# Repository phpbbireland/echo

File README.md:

# echo (Keyboards)
This is the final repository for all prior keyboard development code, and hardware.

Models included are: 
+ Alya: ayla80 (iso/ansi)
+ Cashel: cashel100 (ansi/iso)
+ Mioke: xpad (macro/num pad)
+ Echo: test code for RP2040 ayla80 (iso).
+ EN015_60_AKL (iso)
+ EN014 (iso) June 2025

The current STM32F411 keyboard code works for all versions, however, the RGB is not tested, to put it simply, I don't know how to implement the RGB code as including it resulted in compile errors, best use the RP2040 modulesfor now.  

Moved on to version 2.x of the Keyboard Development Modules (these have a single 34 pin 1.27mm pitch (small) connector), otherwise they are the same...

**Latest Updates**  
I have switched to my RP2040 Development Module as everything works perfectly, no more issues with RGB...  
Going forward, I will use this for all development but may revisit my STM32F411 development board later...

**Important Notes**  
On all my Keyboad PCB's, the 34 pin connetor is mounted on component side (bottom) of PCB.  
On moules with a 34 pin connector, it is mounted on ***bottom*** of PCB, not the component side (top), see image below.  

**Revision C**  

**Revision D**

*Updates:*  
+ Connector now mounted on component side...  
+ Orinitation change 90°...

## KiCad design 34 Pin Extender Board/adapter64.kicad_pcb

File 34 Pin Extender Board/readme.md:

# Extender Board  

34 pin 1.27mm connector to 2 x 20 pin 2.54mm header adapter board.  
Kicad files included...
Gerber files update, previous has mirrored silkscreen...

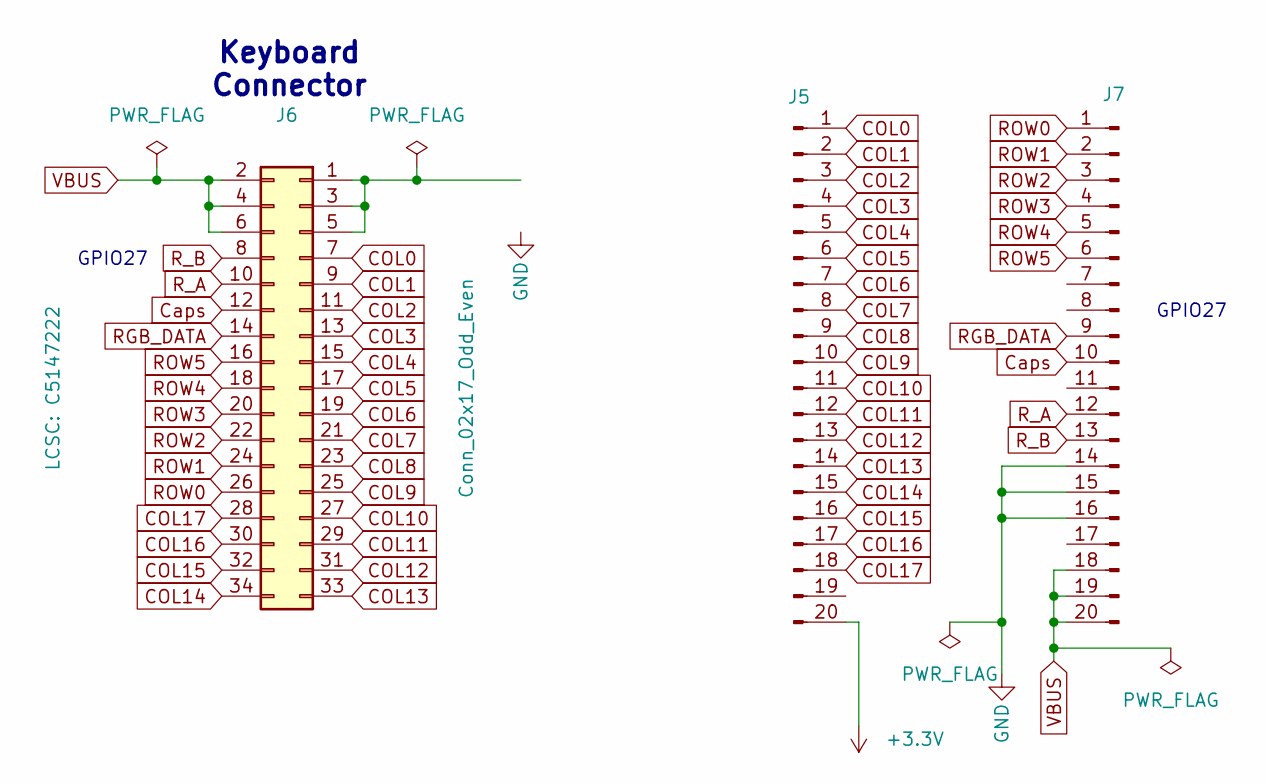
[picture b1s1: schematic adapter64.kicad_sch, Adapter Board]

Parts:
J5, J7: Conn_01x21_Pin; PinSocket_1x21_P2.54mm_Vertical
J6: Conn_02x17_Odd_Even; IDC_2X17_1.27MM; LCSC C5147222

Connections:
+3.3V: J5.20
COL0: J5.1, J6.7
COL1: J5.2, J6.9
COL2: J5.3, J6.11
COL3: J5.4, J6.13
COL4: J5.5, J6.15
COL5: J5.6, J6.17
COL6: J5.7, J6.19
COL7: J5.8, J6.21
COL8: J5.9, J6.23
COL9: J5.10, J6.25
COL10: J5.11, J6.27
COL11: J5.12, J6.29
COL12: J5.13, J6.31
COL13: J5.14, J6.33
COL14: J5.15, J6.34
COL15: J5.16, J6.32
COL16: J5.17, J6.30
COL17: J5.18, J6.28
Caps: J6.12, J7.10
GND: J7.14, J7.15, J7.16
unnamed: J6.1, J6.3, J6.5
RGB_DATA: J6.14, J7.9
ROW0: J6.26, J7.1
ROW1: J6.24, J7.2
ROW2: J6.22, J7.3
ROW3: J6.20, J7.4
ROW4: J6.18, J7.5
ROW5: J6.16, J7.6
R_A: J6.10, J7.12
R_B: J6.8, J7.13
VBUS: J6.2, J6.4, J6.6, J7.18, J7.19, J7.20

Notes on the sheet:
Keyboard Connector
GPIO27

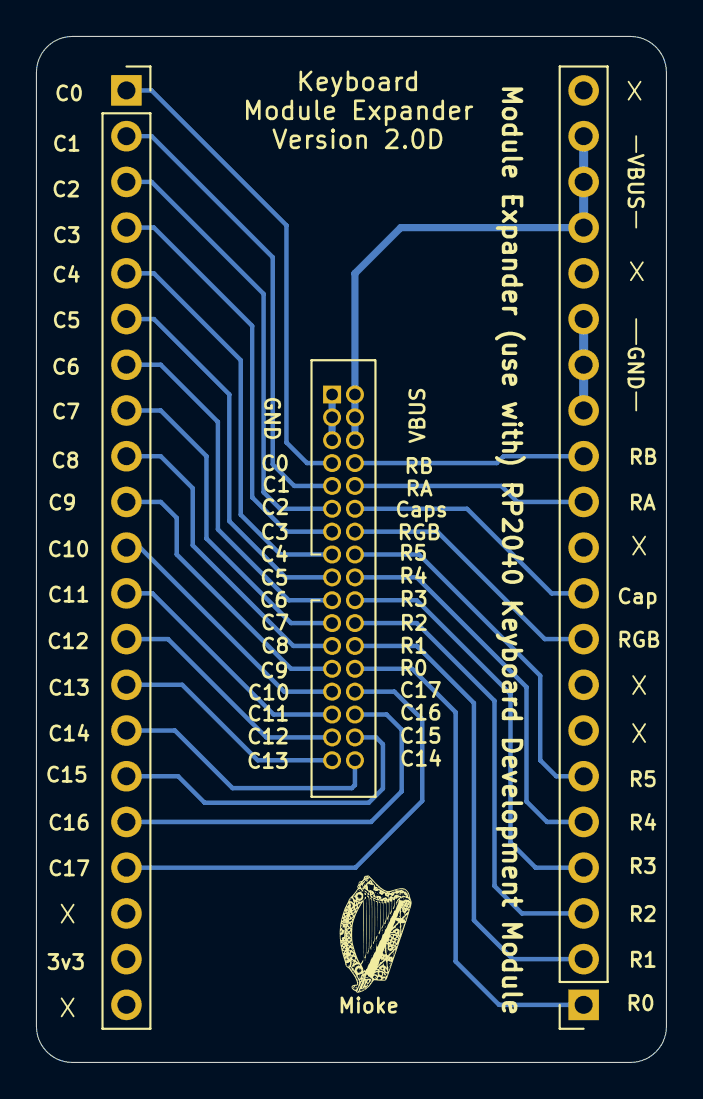
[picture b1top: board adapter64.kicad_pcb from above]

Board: 2 copper layers, 35.0 x 57.0 mm, 3 parts (0 on the bottom side), 31 nets.

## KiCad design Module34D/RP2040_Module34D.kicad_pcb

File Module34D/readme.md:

**Version D**

Micros: RP2040  

Software Supported QMK/VIA: [Link](https://github.com/phpbbireland/echo/tree/main/E014/qmk)  
Switches: MX type hot-swappable  
Keys: Up to 119 Keys (including Macro Keys) + Encoder Switch  
Rotary Encoder: Volume / RGB.  

Tested with [Basic Keyboard](https://github.com/phpbbireland/echo/tree/main/E014)

There are three Keyboard Modules (latest Rev 2D) to give away, thanks to PCBWay, if you are interested in trying out the module, contact me at my [Hackaday Link](https://hackaday.io/project/198392-keyboard-development-module-qmk-via)  

**These files may have updates, please check pin naming and orintation before prooceeding***  
I will update as time allows...

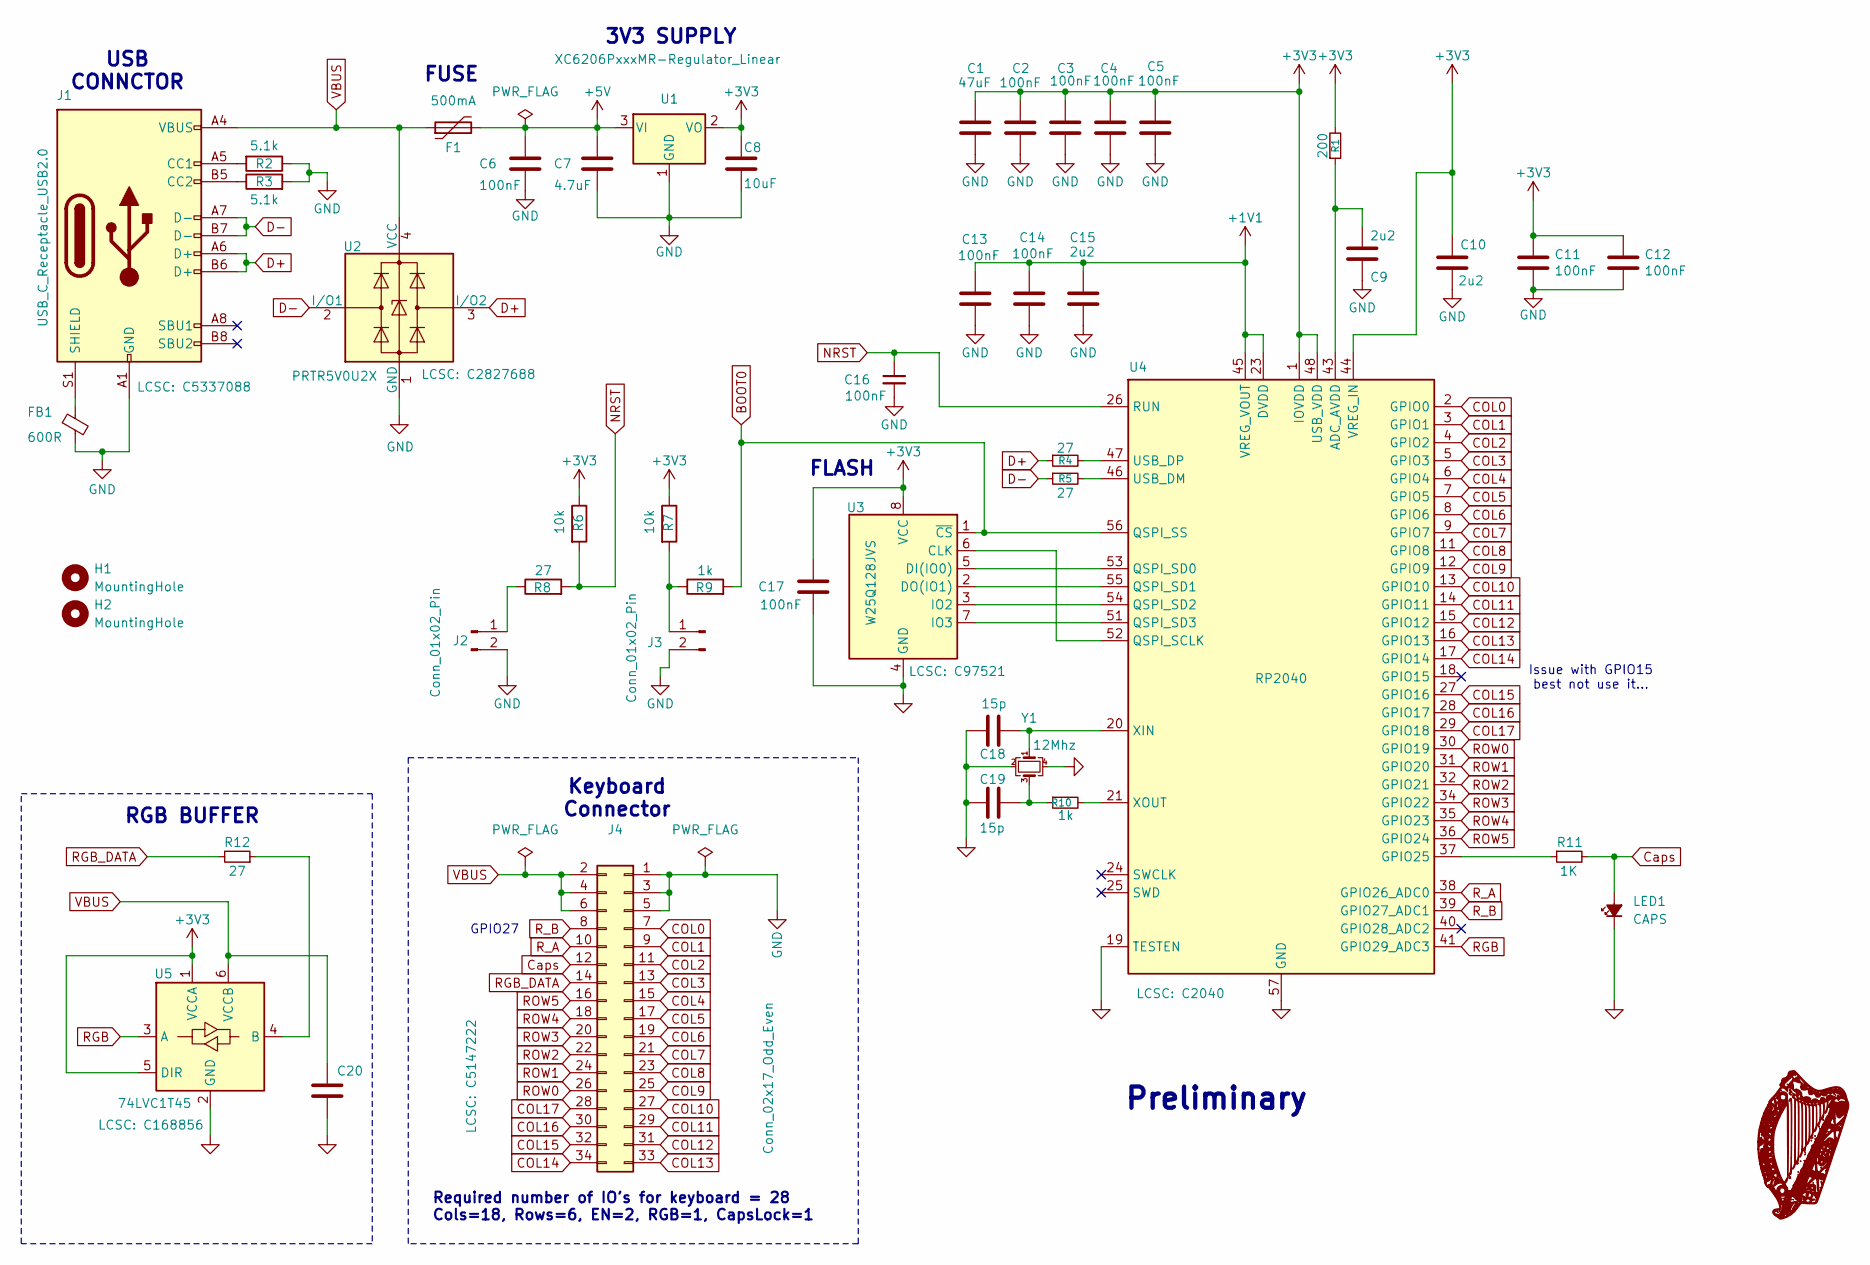
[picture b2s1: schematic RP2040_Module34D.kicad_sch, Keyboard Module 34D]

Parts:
C1: 47uF; C_0805_2012Metric; MPN# CL21A476MQYNNNE; LCSC C16780
C2, C3, C4, C11, C12, C13, C14, C20: 100nF; C_0402_1005Metric; MPN# CL05B104KB54PNC; LCSC C307331
C5, C16, C17: 100nF; C_0402_1005Metric; LCSC C307331
C6: 100nF; C_0402_1005Metric; MPN CL05B104KB54PNC; LCSC C307331
C7: 4.7uF; C_0805_2012Metric; MPN# CL21A475KAQNNNE; LCSC C1779
C8: 10uF; C_0805_2012Metric; LCSC C307331
C9, C10, C15: 2u2; C_0805_2012Metric; MPN# CL21B225KAFNNNE; LCSC C19110
C18: 15p; C_0402_1005Metric; MPN# CL05C150JB5NNNC; LCSC C86285
C19: 15p; C_0402_1005Metric; MPN# CL05C150JB5NNNC; LCSC C307331 OR C86285
F1: 500mA; Fuse_1206_3216Metric; MPN# ASMD1206-150; LCSC C135341
FB1: 600R; BEADC1608X95N; MPN# BLM18AG601SN1D; LCSC C19330
H1, H2: MountingHole; MountingHole_2.2mm_M2
J1: USB_C_Receptacle_USB2.0; USB_C_31-M-12; JlcRotOffset 180
J2, J3: Conn_01x02_Pin; PinHeader_1x02_P2.54mm_Vertical
J4: Conn_02x17_Odd_Even; IDC_2X17_1.27MM; MPN# X1270WV-2x17B-6TV01; LCSC C5147222
LED1: CAPS; LED_0805_2012Metric; MPN# D-B080508B1-KS2; LCSC C108412
R1: 200; R_0402_1005Metric; LCSC# C25087
R2: 5.1k; R_0402_1005Metric; MPN# 0402WGF5101TCE
R3: 5.1k; R_0402_1005Metric; MPN# 0402WGF5101TCE; LCSC C25905
R4, R5: 27; R_0402_1005Metric
R6: 10k; R_0402_1005Metric; MPN# 0402WGF1002TCE; LCSC C25744
R7: 10k; R_0402_1005Metric
R8: 27; R_0402_1005Metric; MPN# 0402WGF270JTCE
R9, R10: 1k; R_0402_1005Metric; MPN# 0402WGF1001TCE; LCSC C11702
R11: 1K; R_0402_1005Metric; MPN# 0402WGF1001TCE; LCSC C11702
R12: 27; R_0402_1005Metric; LCSC C25100
U1: XC6206PxxxMR-Regulator_Linear; SOT-23; LCSC C5446
U2: PRTR5V0U2X; SOT-143; LCSC C2827688
U3: W25Q128JVS; SOIC_128JVSIQ_WIN; Mfr. Part # W25Q128JVSIQ; LCSC C97521
U4: RP2040; QFN-56-1EP_7x7mm_P0.4mm_EP3.2x3.2mm; LCSC C2040
U5: 74LVC1T45; SOT-26; MPN # 74LVC1T45W6-7; JLCPCB_CORRECTION 0; 0; 270
Y1: 12Mhz; Crystal_SMD_3225-4Pin_3.2x2.5mm; LCSC C20625731

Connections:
+1V1: C13.1, C14.1, C15.1, U4.23 (DVDD), U4.45 (VREG_VOUT), U4.50 (DVDD)
+3V3: C1.1, C2.1, C3.1, C4.1, C5.1, C8.1, C10.1, C11.1, C12.1, C17.1, R1.2, R6.1, R7.1, U1.2 (VO), U3.8 (VCC), U4.1 (IOVDD), U4.10 (IOVDD), U4.22 (IOVDD), U4.33 (IOVDD), U4.42 (IOVDD), U4.44 (VREG_IN), U4.48 (USB_VDD), U4.49 (IOVDD), U5.1 (VCCA), U5.5 (DIR)
+5V: C6.1, C7.1, F1.2, U1.3 (VI)
BOOT0: R9.2, U3.1 (~CS), U4.56 (QSPI_SS)
COL0: J4.7, U4.2 (GPIO0)
COL1: J4.9, U4.3 (GPIO1)
COL2: J4.11, U4.4 (GPIO2)
COL3: J4.13, U4.5 (GPIO3)
COL4: J4.15, U4.6 (GPIO4)
COL5: J4.17, U4.7 (GPIO5)
COL6: J4.19, U4.8 (GPIO6)
COL7: J4.21, U4.9 (GPIO7)
COL8: J4.23, U4.11 (GPIO8)
COL9: J4.25, U4.12 (GPIO9)
COL10: J4.27, U4.13 (GPIO10)
COL11: J4.29, U4.14 (GPIO11)
COL12: J4.31, U4.15 (GPIO12)
COL13: J4.33, U4.16 (GPIO13)
COL14: J4.34, U4.17 (GPIO14)
COL15: J4.32, U4.27 (GPIO16)
COL16: J4.30, U4.28 (GPIO17)
COL17: J4.28, U4.29 (GPIO18)
Caps: J4.12, LED1.2 (A), R11.2
D+: J1.A6 (D+), J1.B6 (D+), R4.1, U2.3 (I/O2)
D-: J1.A7 (D-), J1.B7 (D-), R5.1, U2.2 (I/O1)
GND: C1.2, C2.2, C3.2, C4.2, C5.2, C6.2, C7.2, C8.2, C9.2, C10.2, C11.2, C12.2, C13.2, C14.2, C15.2, C16.2, C17.2, C18.2, C19.2, C20.2, FB1.2, J1.A1 (GND), J1.A12 (GND), J1.B1 (GND), J1.B12 (GND), J2.2, J3.2, J4.1, J4.3, J4.5, LED1.1 (K), R2.1, R3.2, U1.1 (GND), U2.1 (GND), U3.4 (GND), U4.19 (TESTEN), U4.57 (GND), U5.2 (GND), Y1.2, Y1.4
NRST: C16.1, R6.2, R8.2, U4.26 (RUN)
unnamed: C19.1, R10.1, Y1.3
unnamed: J1.A5 (CC1), R2.2
unnamed: J1.B5 (CC2), R3.1
unnamed: FB1.1, J1.S1 (SHIELD)
unnamed: J2.1, R8.1
unnamed: J3.1, R7.2, R9.1
unnamed: U3.6 (CLK), U4.52 (QSPI_SCLK)
unnamed: U3.5 (DI(IO0)), U4.53 (QSPI_SD0)
unnamed: U3.2 (DO(IO1)), U4.55 (QSPI_SD1)
unnamed: U3.3 (IO2), U4.54 (QSPI_SD2)
unnamed: U3.7 (IO3), U4.51 (QSPI_SD3)
unnamed: C9.1, R1.1, U4.43 (ADC_AVDD)
unnamed: R11.1, U4.37 (GPIO25)
unnamed: R5.2, U4.46 (USB_DM)
unnamed: R4.2, U4.47 (USB_DP)
unnamed: C18.1, U4.20 (XIN), Y1.1
unnamed: R10.2, U4.21 (XOUT)
unnamed: R12.1, U5.4 (B)
RGB: U4.41 (GPIO29_ADC3), U5.3 (A)
RGB_DATA: J4.14, R12.2
ROW0: J4.26, U4.30 (GPIO19)
ROW1: J4.24, U4.31 (GPIO20)
ROW2: J4.22, U4.32 (GPIO21)
ROW3: J4.20, U4.34 (GPIO22)
ROW4: J4.18, U4.35 (GPIO23)
ROW5: J4.16, U4.36 (GPIO24)
R_A: J4.10, U4.38 (GPIO26_ADC0)
R_B: J4.8, U4.39 (GPIO27_ADC1)
VBUS: C20.1, F1.1, J1.A4 (VBUS), J1.A9 (VBUS), J1.B4 (VBUS), J1.B9 (VBUS), J4.2, J4.4, J4.6, U2.4 (VCC), U5.6 (VCCB)

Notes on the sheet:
Preliminary
FLASH
FUSE
Keyboard Connector
Issue with GPIO15 best not use it...
3V3 SUPPLY
USB CONNCTOR
GPIO27
RGB BUFFER
Required number of IO's for keyboard = 28 Cols=18, Rows=6, EN=2, RGB=1, CapsLock=1

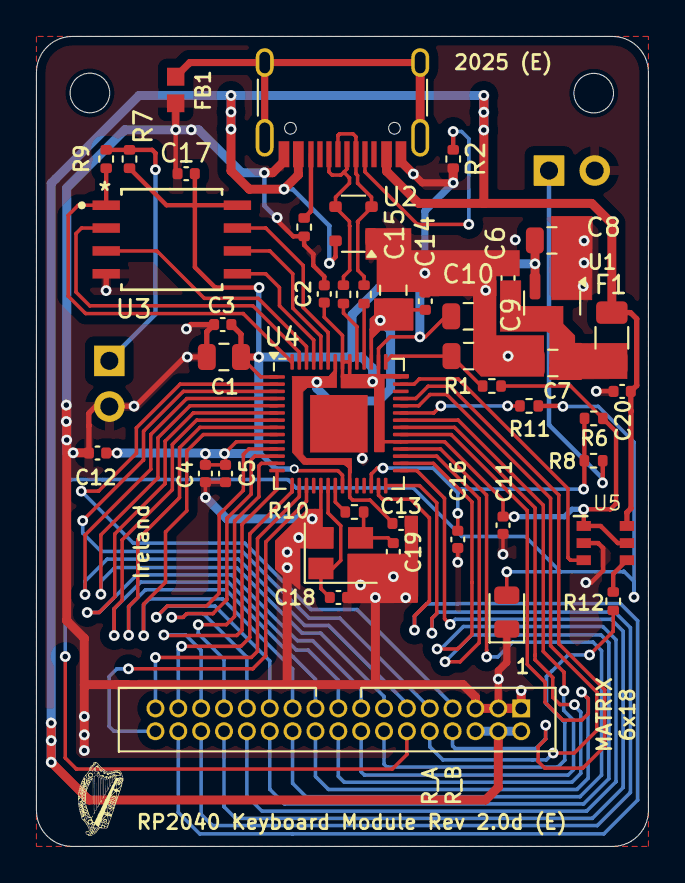
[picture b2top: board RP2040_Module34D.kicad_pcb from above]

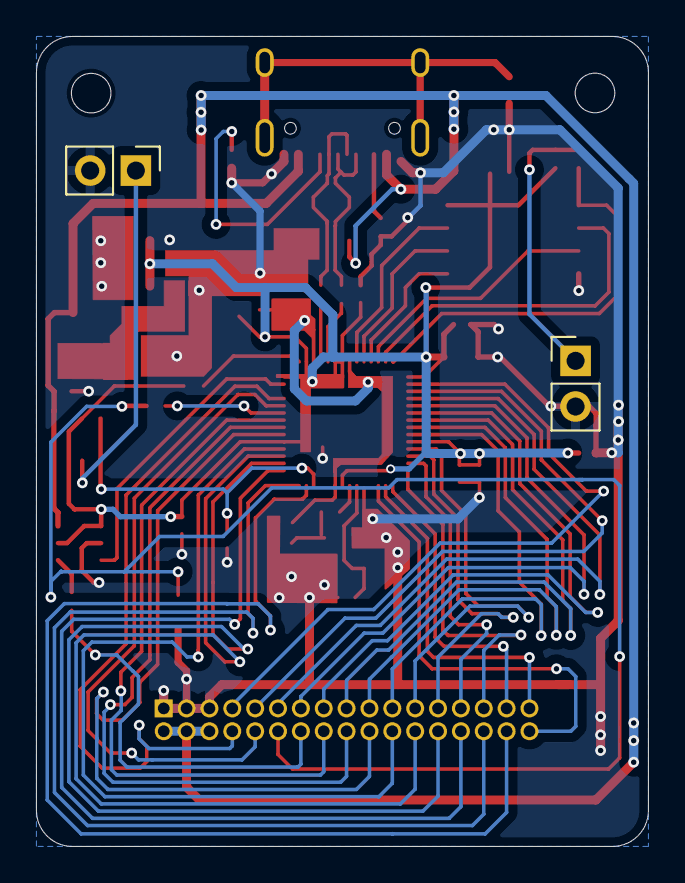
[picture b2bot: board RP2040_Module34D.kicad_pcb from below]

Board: 2 copper layers, 34.0 x 45.0 mm, 47 parts (2 on the bottom side), 56 nets.

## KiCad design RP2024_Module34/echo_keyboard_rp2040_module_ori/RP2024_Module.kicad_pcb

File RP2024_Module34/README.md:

# echo
Files to build the Basic Keyboard and RP2040 Keyboard Development Module

These have been tested with the current code and work flawlessly...
Included: 
+ RP2040_Fullsize_PCBWay_barebones... Basic Keyboard files used in all testing...
+ echo_keyboard_rp2040_module... Slightly smaller module, not produced yet...
+ echo_keyboard_rp2040_module_ori... This is the fully tested module I used in the build. [Image](https://github.com/phpbbireland/echo/blob/main/RP2024_Module34/images/RP2024_Module_Rev0.1.png)
+ iso_encoder_rp2040_en017_brd2...   The QMK and Via code for the project...

A couple of these boards are available (version 1.0, the one with the four RGB leds on it) just contact me...

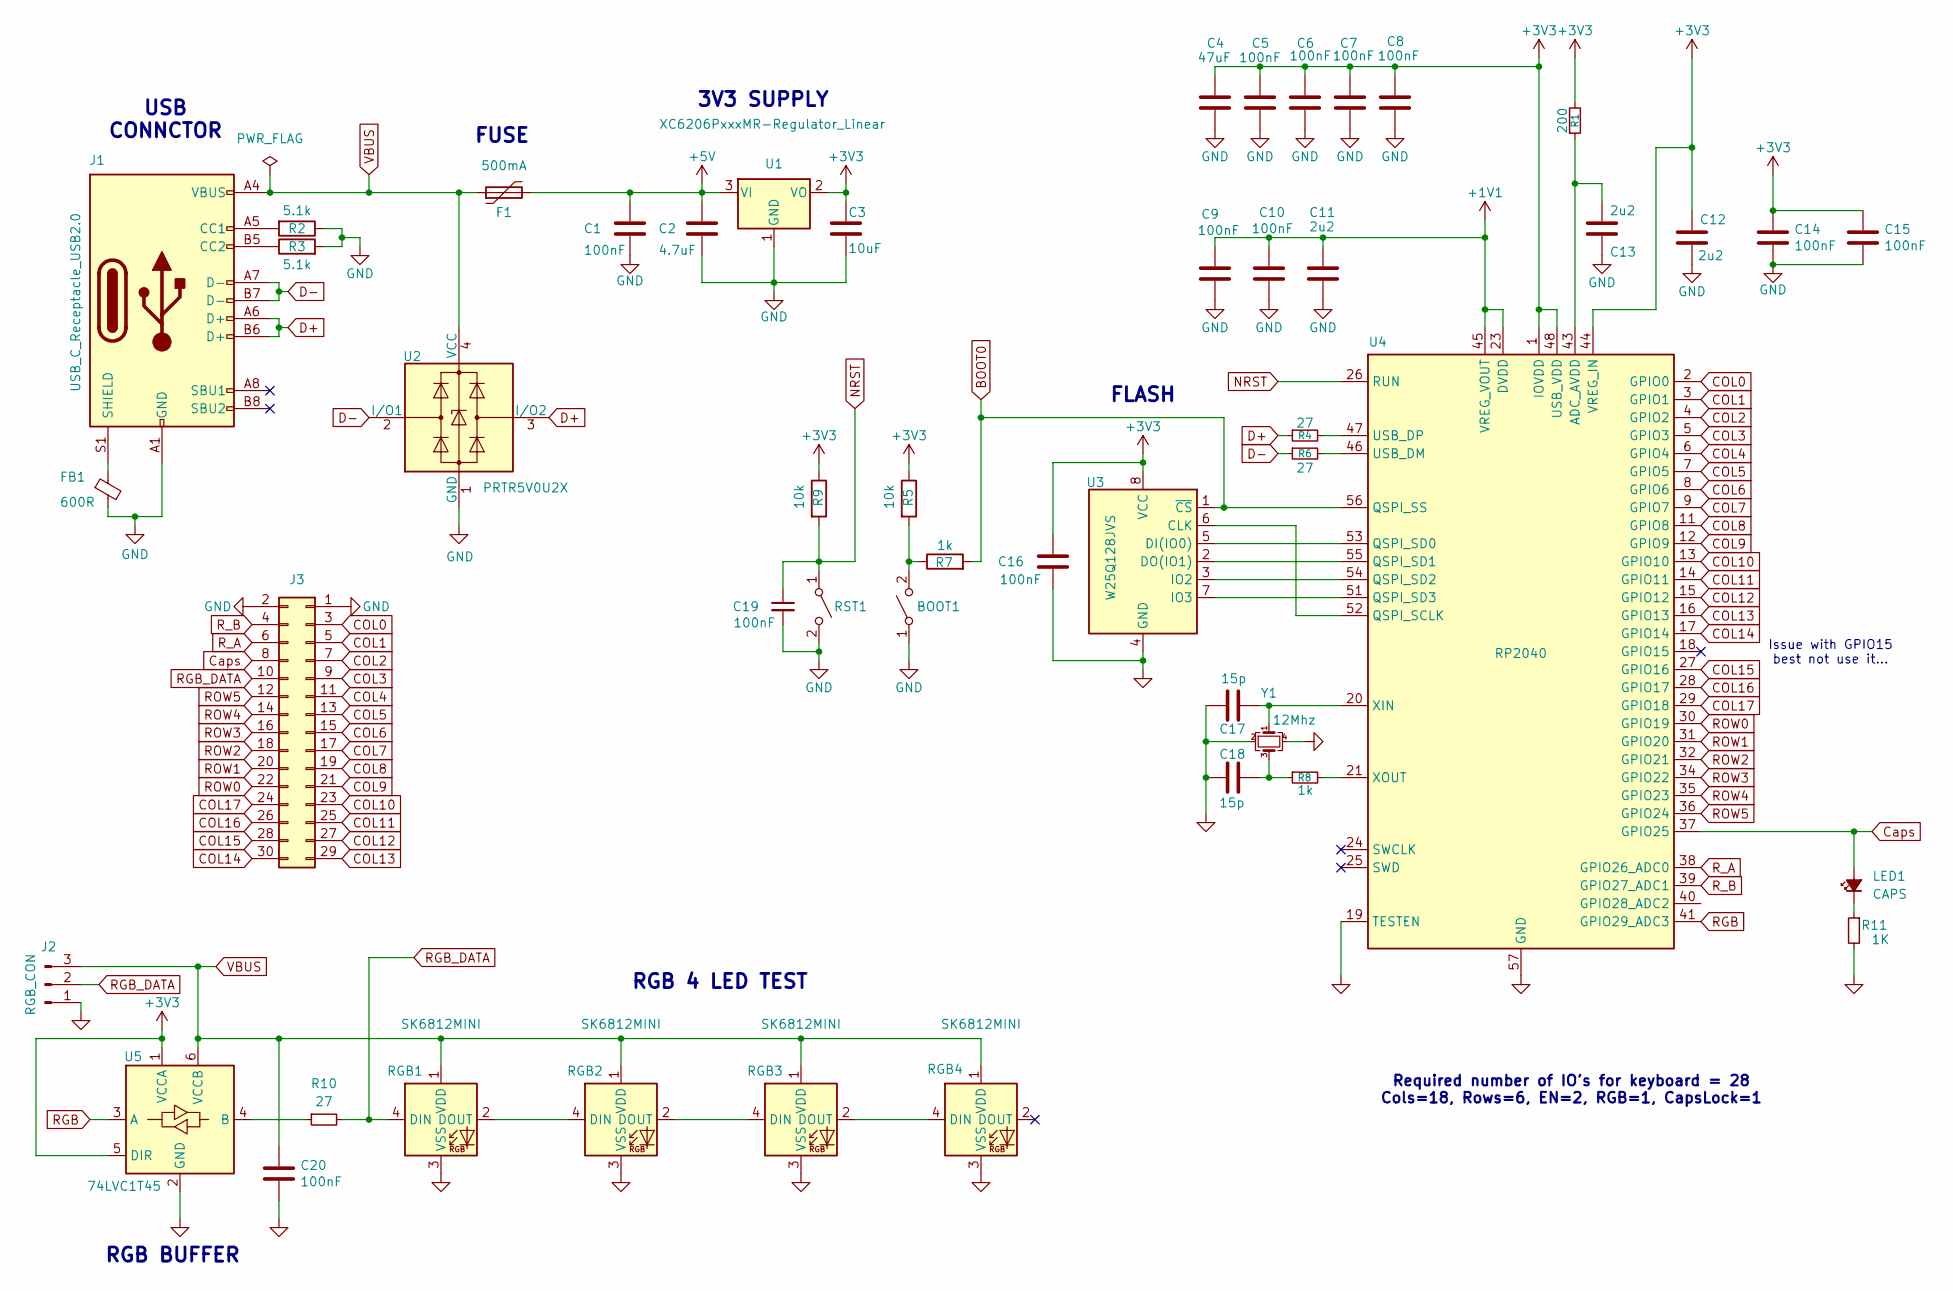
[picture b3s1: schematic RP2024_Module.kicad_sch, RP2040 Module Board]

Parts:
BOOT1: SW_SPST; SW_SPST_TL3342
C1, C5, C6, C7, C8, C9, C10, C14, C15, C16, C19, C20: 100nF; C_0402_1005Metric; LCSC C307331
C2: 4.7uF; C_0805_2012Metric; LCSC C307331
C3: 10uF; C_0805_2012Metric; LCSC C307331
C4: 47uF; C_0805_2012Metric; LCSC C307331
C11, C12, C13: 2u2; C_0805_2012Metric; LCSC C307331
C17, C18: 15p; C_0402_1005Metric; LCSC C307331
F1: 500mA; Fuse_1206_3216Metric; LCSC C135341
FB1: 600R; BEADC1608X95N
J1: USB_C_Receptacle_USB2.0; USB_C_31-M-12; JlcRotOffset 180
J2: RGB_CON; JST_EH_S3B-EH_1x03_P2.50mm_Horizontal; LCSC C263754
J3: Conn_02x15_Odd_Even; IDC_2X15_1.27MM; LCSC C5121680
LED1: CAPS; LED_0805_2012Metric
R1: 200; R_0402_1005Metric
R2, R3: 5.1k; R_0402_1005Metric
R4, R6: 27; R_0402_1005Metric
R5, R9: 10k; R_0402_1005Metric
R7, R8: 1k; R_0402_1005Metric
R10: 27; R_0402_1005Metric; LCSC C25100
R11: 1K; R_0402_1005Metric
RGB1: SK6812MINI; LED_SK6812MINI; LCSC C5149201
RGB2, RGB3, RGB4: SK6812MINI; LED_SK6812MINI
RST1: SW_SPST; SW_SPST_TL3342
U1: XC6206PxxxMR-Regulator_Linear; SOT-23; LCSC C5446
U2: PRTR5V0U2X; SOT-143; LCSC C2827688
U3: W25Q128JVS; SOIC_128JVSIQ_WIN; Mfr. Part # W25Q128JVSIQ; LCSC C97521
U4: RP2040; QFN-56-1EP_7x7mm_P0.4mm_EP3.2x3.2mm; LCSC C2040
U5: 74LVC1T45; SOT-26; MPN 74LVC1T45W6-7; JLCPCB_CORRECTION 0; 0; 270
Y1: 12Mhz; Crystal_SMD_3225-4Pin_3.2x2.5mm; LCSC C20625731

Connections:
+1V1: C9.1, C10.1, C11.1, U4.23 (DVDD), U4.45 (VREG_VOUT), U4.50 (DVDD)
+3V3: C3.1, C4.1, C5.1, C6.1, C7.1, C8.1, C12.1, C14.1, C15.1, C16.1, R1.2, R5.1, R9.1, U1.2 (VO), U3.8 (VCC), U4.1 (IOVDD), U4.10 (IOVDD), U4.22 (IOVDD), U4.33 (IOVDD), U4.42 (IOVDD), U4.44 (VREG_IN), U4.48 (USB_VDD), U4.49 (IOVDD), U5.1 (VCCA), U5.5 (DIR)
+5V: C1.1, C2.1, F1.2, U1.3 (VI)
BOOT0: R7.2, U3.1 (~CS), U4.56 (QSPI_SS)
COL0: J3.3, U4.2 (GPIO0)
COL1: J3.5, U4.3 (GPIO1)
COL2: J3.7, U4.4 (GPIO2)
COL3: J3.9, U4.5 (GPIO3)
COL4: J3.11, U4.6 (GPIO4)
COL5: J3.13, U4.7 (GPIO5)
COL6: J3.15, U4.8 (GPIO6)
COL7: J3.17, U4.9 (GPIO7)
COL8: J3.19, U4.11 (GPIO8)
COL9: J3.21, U4.12 (GPIO9)
COL10: J3.23, U4.13 (GPIO10)
COL11: J3.25, U4.14 (GPIO11)
COL12: J3.27, U4.15 (GPIO12)
COL13: J3.29, U4.16 (GPIO13)
COL14: J3.30, U4.17 (GPIO14)
COL15: J3.28, U4.27 (GPIO16)
COL16: J3.26, U4.28 (GPIO17)
COL17: J3.24, U4.29 (GPIO18)
Caps: J3.8, LED1.2 (A), U4.37 (GPIO25)
D+: J1.A6 (D+), J1.B6 (D+), R4.1, U2.3 (I/O2)
D-: J1.A7 (D-), J1.B7 (D-), R6.1, U2.2 (I/O1)
GND: BOOT1.1 (A), C1.2, C2.2, C3.2, C4.2, C5.2, C6.2, C7.2, C8.2, C9.2, C10.2, C11.2, C12.2, C13.2, C14.2, C15.2, C16.2, C17.2, C18.2, C19.2, C20.2, FB1.2, J1.A1 (GND), J1.A12 (GND), J1.B1 (GND), J1.B12 (GND), J2.1, J3.1, J3.2, R2.1, R3.2, R11.2, RGB1.3 (VSS), RGB2.3 (VSS), RGB3.3 (VSS), RGB4.3 (VSS), RST1.2 (B), U1.1 (GND), U2.1 (GND), U3.4 (GND), U4.19 (TESTEN), U4.57 (GND), U5.2 (GND), Y1.2, Y1.4
NRST: C19.1, R9.2, RST1.1 (A), U4.26 (RUN)
unnamed: BOOT1.2 (B), R5.2, R7.1
unnamed: C18.1, R8.1, Y1.3
unnamed: J1.A5 (CC1), R2.2
unnamed: J1.B5 (CC2), R3.1
unnamed: FB1.1, J1.S1 (SHIELD)
unnamed: LED1.1 (K), R11.1
unnamed: RGB1.2 (DOUT), RGB2.4 (DIN)
unnamed: RGB2.2 (DOUT), RGB3.4 (DIN)
unnamed: RGB3.2 (DOUT), RGB4.4 (DIN)
unnamed: U3.6 (CLK), U4.52 (QSPI_SCLK)
unnamed: U3.5 (DI(IO0)), U4.53 (QSPI_SD0)
unnamed: U3.2 (DO(IO1)), U4.55 (QSPI_SD1)
unnamed: U3.3 (IO2), U4.54 (QSPI_SD2)
unnamed: U3.7 (IO3), U4.51 (QSPI_SD3)
unnamed: C13.1, R1.1, U4.43 (ADC_AVDD)
unnamed: R6.2, U4.46 (USB_DM)
unnamed: R4.2, U4.47 (USB_DP)
unnamed: C17.1, U4.20 (XIN), Y1.1
unnamed: R8.2, U4.21 (XOUT)
unnamed: R10.1, U5.4 (B)
RGB: U4.41 (GPIO29_ADC3), U5.3 (A)
RGB_DATA: J2.2, J3.10, R10.2, RGB1.4 (DIN)
ROW0: J3.22, U4.30 (GPIO19)
ROW1: J3.20, U4.31 (GPIO20)
ROW2: J3.18, U4.32 (GPIO21)
ROW3: J3.16, U4.34 (GPIO22)
ROW4: J3.14, U4.35 (GPIO23)
ROW5: J3.12, U4.36 (GPIO24)
R_A: J3.6, U4.38 (GPIO26_ADC0)
R_B: J3.4, U4.39 (GPIO27_ADC1)
VBUS: C20.1, F1.1, J1.A4 (VBUS), J1.A9 (VBUS), J1.B4 (VBUS), J1.B9 (VBUS), J2.3, RGB1.1 (VDD), RGB2.1 (VDD), RGB3.1 (VDD), RGB4.1 (VDD), U2.4 (VCC), U5.6 (VCCB)

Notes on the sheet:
USB CONNCTOR
RGB BUFFER
FLASH
RGB 4 LED TEST
3V3 SUPPLY
FUSE
Issue with GPIO15 best not use it...
Required number of IO's for keyboard = 28 Cols=18, Rows=6, EN=2, RGB=1, CapsLock=1

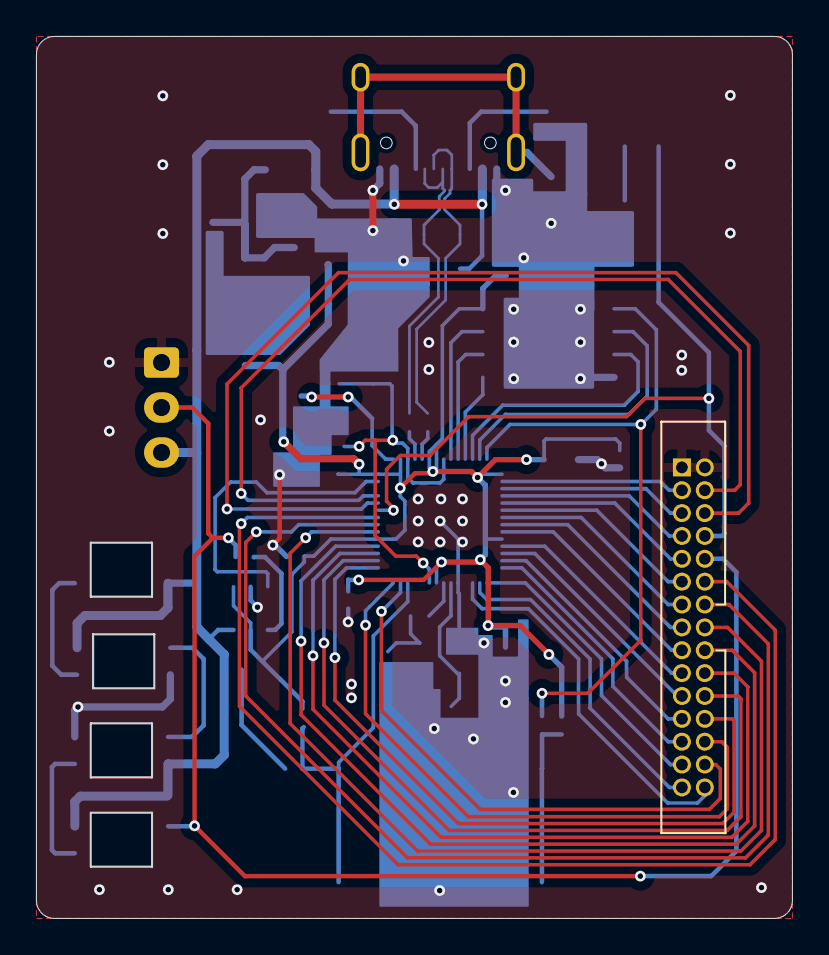
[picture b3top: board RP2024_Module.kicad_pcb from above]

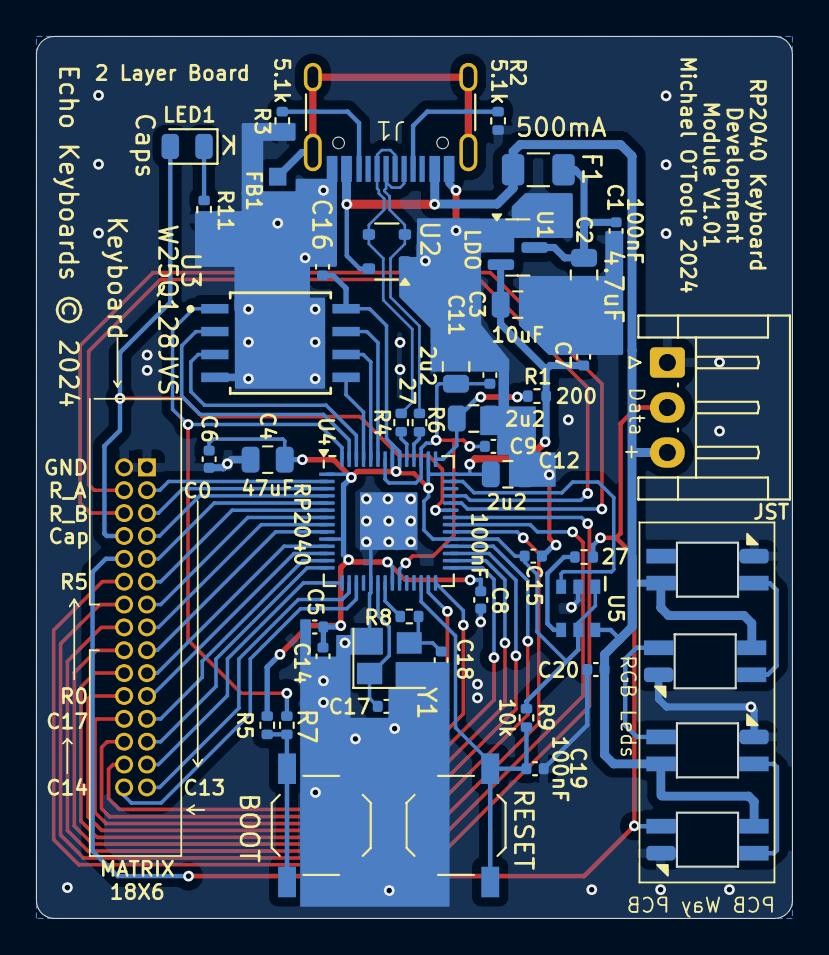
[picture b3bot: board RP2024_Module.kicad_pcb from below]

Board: 2 copper layers, 41.9 x 48.9 mm, 49 parts (44 on the bottom side), 58 nets.

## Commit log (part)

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2024-11-17 Delete iso_encoder/store/echo.json.bak
    not required
2024-11-29 Update keymap.c
    update to current tested code
2024-11-29 Update keyboard.json
    updated layout code
2024-11-29 Delete iso_encoder/store/usevia-image-iso.png
    moved
2024-11-29 Delete iso_encoder/store/usevia-image-ansi.png
    moved
2024-11-29 Delete iso_encoder/store/fromusevia.app-echo_keyboard_v3.layout.json
    moved
2024-11-29 Delete iso_encoder/store/from-kle.com-echo-v3.json
    moved
2024-11-29 Delete iso_encoder/store/ayla80.layout.json
    moved
2024-11-29 Delete iso_encoder/store/echo.layout.c
    moved
2024-11-29 Delete iso_encoder/store/echo.layout.json
    moved
2024-11-29 Add files via upload
    Moved files
2024-11-29 Delete iso_encoder/store/makeit
    not required
2024-11-29 Kicad Files
2024-11-29 Delete Echo_Ayla_Final/pcbway_production/2024-11-14-18-09-35/NewMXtest.kicad_pcb_gerber.zip
    Old file, will replace
2024-11-29 Add files via upload
    Kicad Files
2024-11-29 Delete iso_encoder/Echo_Ayla_Final/pcbway_production/2024-11-14-18-09-35/NewMXtest.kicad_pcb_gerber.zip
    Removed as it requires updating
2024-12-11 Update keyboard.json
    Testing code for RGB matrix...
    Altered ROWS/COLS...
2024-12-11 Update mcuconf.h
    Add code for RGB
2024-12-11 Update echo.h
    temp file
2024-12-15 Add RP2040
2024-12-15 Add RP2040 (RGBLIGHT)
2024-12-15 update image
2024-12-26 Update info.jsonrearrange code
2024-12-26 Delete iso_encoder_rp2040/info.json.bak
    Not required
2024-12-26 Delete iso_encoder_rp2040/keyboard.json.bak
    Not required
2024-12-26 Update keymap.c
    removed empty lines
2024-12-26 Delete iso_encoder_rp2040/compilereport
    not required
2024-12-26 Update config.h
    Reduced RGB led count as SCRLK (OR PAUSE) not populated (replaced with encoder on right)
2025-01-10 Create Matrix
2025-01-10 Update Matrix
2025-01-29 Update notes
2025-01-29 Create temp
2025-01-29 Screenshop of useiav.app
2025-01-29 keyboard layout editor image
2025-01-29 keyboard layout editor site image
2025-01-29 keyboard layout editor .com image
2025-02-14 Update config.h
    Add flip encoder
2025-02-14 Update keyboard.json
    Correct RGB layout
2025-02-14 Add files via upload
    Keyboard Development Module Rev 2.0
2025-02-14 Add files via upload
    Code for Module Board
2025-02-14 Create readme.md
    Note on connector and current for RGB
2025-02-19 Create layout_current.json
    Temp_file_matrix
2025-02-19 Update layout_current.json
    All correct for er2
2025-02-19 Update keyboard.json
    Everything correct and working...
2025-02-19 Update config.h
    Added 1 rgb led to count
2025-02-19 Add files via upload
    File renamed
2025-02-19 Delete iso_encoder_rp2040_er2/rgb files/iso_encoder_rp2040_er2.c
    No longer required
2025-02-19 Delete iso_encoder_rp2040_er2/rgb files/iso_encoder_rp2040_er2.h
    no longer required
2025-02-19 Delete iso_encoder_rp2040_er2/notes
    Not required
2025-02-19 Update readme.md
    Keyboard code complete, everything tested... 100% working...
2025-02-19 Update readme.md
    fixed rgb effects...
2025-02-19 Update usevia_en017_brd2.json
    add effects
2025-02-19 Update keyboard.json
    added effects
2025-02-19 Add files via upload
    updated image
2025-02-19 Delete RP2024_Module34/iso_encoder_rp2040_en017_brd2/via.json
    Not required
2025-02-19 Delete RP2024_Module34/iso_encoder_rp2040_en017_brd2/kle_echo-en017_brd2.json
    Not required
2025-02-19 Add files via upload
    Basic Keyboard Kicad Files
2025-02-19 Create readme.md
    Files to make the Basic Keyboard
2025-02-19 Add files via upload
    missed this in upload....
2025-02-19 Add files via upload
    Move file here
2025-02-19 Delete RP2024_Module34/RP2024_Module34.kicad_pcb
    moved
2025-02-19 Delete RP2024_Module34/RP2024_Module34.kicad_prl
    moved
2025-02-19 Delete RP2024_Module34/RP2024_Module34.kicad_pro
    moved
2025-02-19 Delete RP2024_Module34/RP2024_Module34.kicad_sch
    moved
2025-02-19 Add files via upload
    Original Module image added
2025-02-19 Add files via upload
    Original with test RGB leds
2025-02-19 Add files via upload
    This is the module fully tested and working, the original
2025-02-20 Add files via upload
    Final 34C
2025-02-20 Delete RP2024_Module34/echo_keyboard_rp2040_module/Module34C.png
    Updating
2025-02-20 Add files via upload
    Updated
2025-03-21 Files to create the extender board
2025-03-21 Add files via upload
    Added Gerber Files
2025-03-22 AKKO M1 Like Layout 60%
2025-03-22 Add files via upload
    Plate Graphic Files
2025-03-22 KLE Layout Image
2025-05-08 Update readme.md
    New PC build and OS install, I might need these...
2025-06-18 Add files via upload
    Latest and last EN014 Basic Keyboard with 32 pin connector, uses rev 2.0 module
2025-06-18 Add files via upload
    DFX file for Plate
2025-06-18 Create KLE_EN014_RawDataFile
    Added Keyboard Editors raw data file.
2025-06-24 Electronic Files for qmk
2025-06-24 qmk files for en014
2025-06-24 Update keyboard.json
    Fixed RGB matrix (even rows were reversed)...
2025-06-27 Delete E014/qmk/echo.c
    Not required
2025-06-27 Delete E014/qmk/echo.h
    Not required
2025-06-27 Delete E014/qmk/temp
    Removed temp file
2025-06-27 Update readme.md
    Added notes on 3d printed case
2025-07-01 Update README.md
    Added some images
2025-07-03 Add files via upload
    Module 34C
2025-07-03 Add files via upload
    Keyboard Layout Editor image
2025-07-21 Update README.md
    Moved some info
2025-07-21 Update readme.md
    Moved 3d case info to main page
2025-07-22 Add files via upload
    Printed Plate
2025-12-02 Update config.h
    Flip encoder, add caps lock pin
2025-12-17 Rev D files
2025-12-17 Update README.md
    Added version D
2026-01-14 Delete 34 Pin Extender Board/adapter64.kicad_pcb_gerber.zip
    Wrong Silkscreen (mirored)
2026-01-14 Add files via upload
    Updated gerbers
2026-01-14 Add files via upload
    Updates

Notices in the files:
RP2024_Module34/echo_keyboard_rp2040_module_ori/RP2024_Module.kicad_pcb:
Echo Keyboards © 2024
